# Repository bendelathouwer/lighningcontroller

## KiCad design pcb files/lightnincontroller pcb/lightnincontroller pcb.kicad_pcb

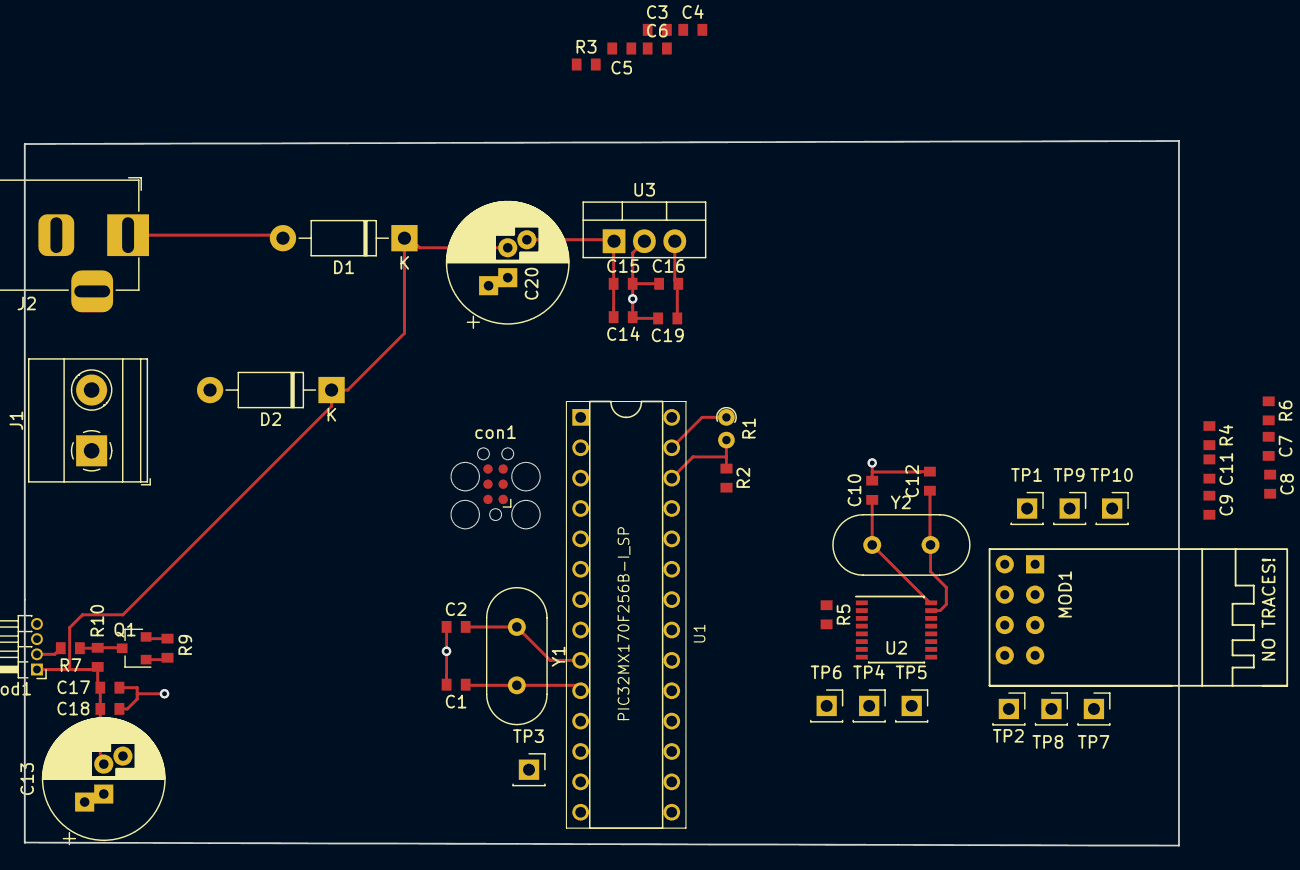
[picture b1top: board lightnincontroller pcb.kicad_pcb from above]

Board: 2 copper layers, 96.5 x 58.9 mm, 52 parts (0 on the bottom side), 27 nets.

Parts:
C1, C2, C3, C4, C5, C6, C7, C8, C9, C10, C11, C12, C14, C15, C16, C19: C_Small; C_0603_1608Metric
C13: C; CP_Radial_D10.0mm_P2.50mm_P5.00mm
C17, C18: C; C_0603_1608Metric
C20: C_Small; CP_Radial_D10.0mm_P2.50mm_P5.00mm
D1, D2: 1N4004; D_DO-41_SOD81_P10.16mm_Horizontal
J1: Screw_Terminal_01x02; TerminalBlock_Phoenix_MKDS-1,5-2-5.08_1x02_P5.08mm_Horizont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
J2: Barrel_Jack; BarrelJack_Horizontal
MOD1: ESP8266; esp8266mod
Q1: BSS138; SOT-23
R1: R_PHOTO; R_Axial_DIN0204_L3.6mm_D1.6mm_P1.90mm_Vertical
R2, R3, R4, R5, R6, R7, R9, R10: R; R_0603_1608Metric
TP1, TP2, TP3, TP4, TP5, TP6, TP7, TP8, TP9, TP10: Test_Point; PinSocket_1x01_P2.54mm_Vertical
U1: PIC32MX170F256B-I_SP; DIP28-2.54-34.7X7.62MM
U2: TSSOP16-SC16IS740IPW; SSOP-16_4.4x5.2mm_P0.65mm
U3: 7833; TO-220-3_Vertical
Y1, Y2: Crystal; Crystal_HC49-4H_Vertical
con1: icsp; Tag-Connect_TC2030-IDC-FP_2x03_P1.27mm_Vertical
mod1: Neopixel; PinHeader_1x04_P1.27mm_Horizontal

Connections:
+3V3: C4.1, C5.1, C7.1, C8.1, C9.1, C11.1, C16.2, C19.1, MOD1.7, Q1.1, R1.1, R3.1, R4.1, R5.1, R6.1, R9.1, U1.8, U1.19, U1.27, U2.1, U2.2, U2.3, U2.8, U3.3, con1.3
/ESP8266/CH_PD: MOD1.3, TP10.1, U1.25
/ESP8266/GPIO2: MOD1.4, TP9.1, U1.24
/ESP8266/RESET: R4.2, TP3.1, U1.12, U2.14
/ESP8266/RX: MOD1.8, TP2.1, U2.12
/ESP8266/SCL: R5.2, TP4.1, U1.7, U2.5
/ESP8266/SDA: R6.2, TP6.1, U1.6, U2.6
/ESP8266/TX: MOD1.1, TP1.1, U2.13
/ESP8266/XTAL1: C12.1, U2.15, Y2.2
/ESP8266/XTAL2: C10.1, U2.16, Y2.1
/ESP8266/~IRQ: TP5.1, U1.11, U2.7
/Neopixel/DI: Q1.3, R7.1, R10.2
/controller/GPIO0: MOD1.6, TP7.1, U1.22
/controller/NEOPIX_OUT1: Q1.2, R9.2, U1.21
/controller/PGEC1: U1.5, con1.6
/controller/PGED1: U1.4, con1.4
/controller/PhotoCel: R1.2, R2.1, U1.26
/controller/RST: MOD1.5, TP8.1, U1.23
/controller/~MCLR: C3.1, R3.2, U1.1, con1.1
GND: C1.2, C2.1, C3.2, C4.2, C5.2, C6.1, C7.2, C8.2, C9.2, C10.2, C11.2, C12.2, C13.1, C14.1, C15.2, C16.1, C17.2, C18.1, C19.2, C20.1, J1.1, J2.2, J2.3, MOD1.2, R2.2, U1.13, U1.28, U2.9, U3.2, con1.2, mod1.3, mod1.4
unnamed: C1.1, U1.10, Y1.2
unnamed: C2.2, U1.9, Y1.1
unnamed: C6.2, U1.20
unnamed: D1.2, J2.1
unnamed: D2.2, J1.2
unnamed: R7.2, mod1.2
VCC: C13.2, C14.2, C15.1, C17.1, C18.2, C20.2, D1.1, D2.1, R10.1, U3.1, mod1.1

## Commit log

2018-09-01 pcb files
    added pcb files to the repo
2018-10-18 controller
    verder getekend aan men controller
2018-10-20 schemerdetectie
    schemerdetectie toegevoegd
2018-10-27 esp en ds1307
    gestart aan ds1307 interface
2018-10-27 RTC
    RTC afgetekend
2018-11-10 lightning controller
    lightining controller allen neopixels af te tekenen +voeding
2018-11-25 neopixel
    neopixels ingetekend
2018-12-21 7833
    voeding en neopixls verbeterd
2018-12-24 3de bodys toegevoed
    pcb 3d view body;s toegevoegd
2019-01-01 pic
    pic controller en co gerouted
